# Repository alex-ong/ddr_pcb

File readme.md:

DDR FSR PCB
===

A simple pcb that fits into a smaller footprint than a half-sized breadboard. Measurements are 49mm x 62mm

Uses screw terminals for wires and sip sockets for resistors to make everything tool-less once soldered.

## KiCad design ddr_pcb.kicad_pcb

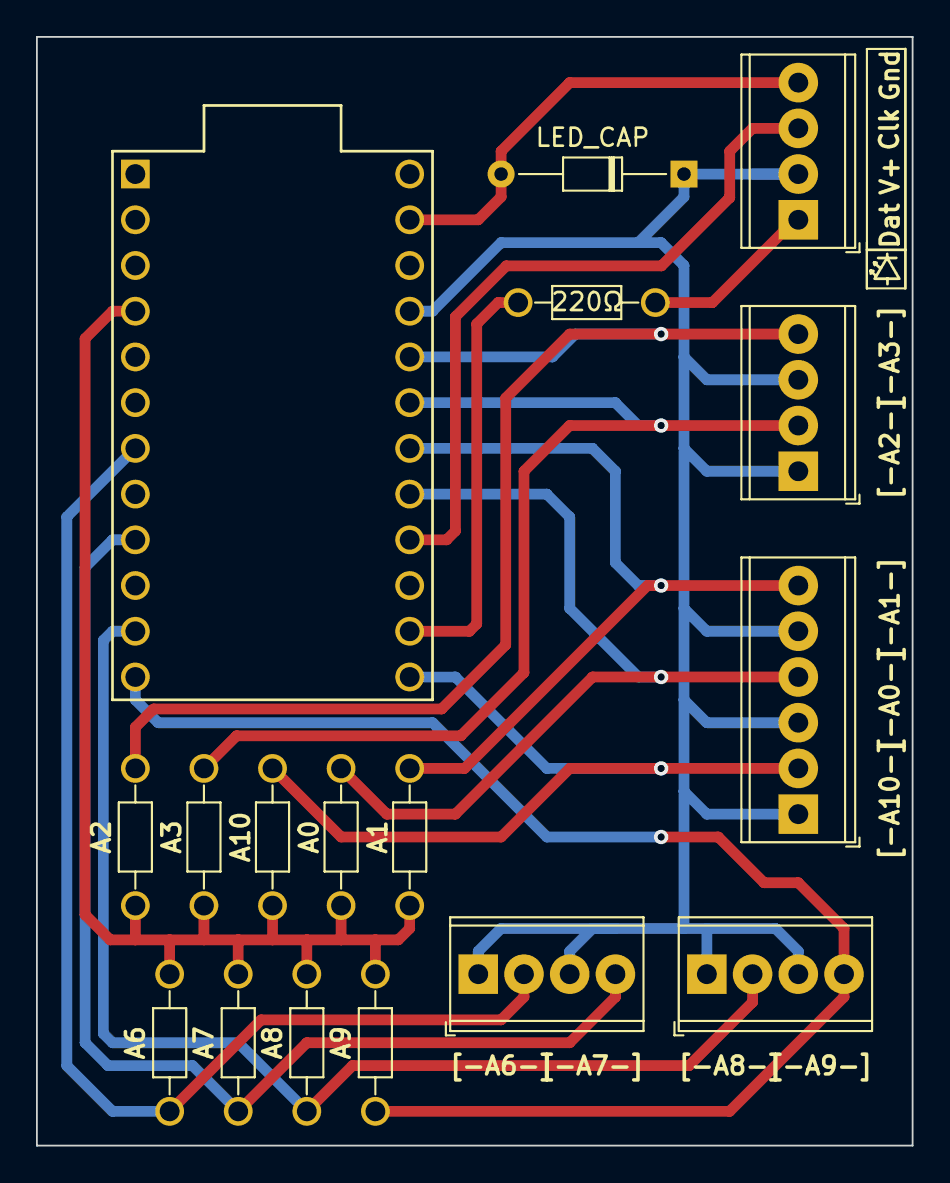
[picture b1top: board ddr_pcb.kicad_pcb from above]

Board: 2 copper layers, 48.7 x 61.6 mm, 17 parts (0 on the bottom side), 15 nets.

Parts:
220Ω: R_Small; R_Axial_DDRPAD_L3.6mm_D1.6mm_P7.62mm_Horizontal
A0, A1, A2, A3, A6, A7, A8, A9, A10: R_Small; R_Axial_DDRPAD_L3.6mm_D1.6mm_P7.62mm_Horizontal
J1, J2, J3, J5: Screw_Terminal_01x04; TerminalBlock_Phoenix_MPT-0,5-4-2.54_1x04_P2.54mm_Horizontal
J4: Screw_Terminal_01x06; TerminalBlock_Phoenix_MPT-0,5-6-2.54_1x06_P2.54mm_Horizontal
LED_CAP: CP; D_DO-34_SOD68_P10.16mm_Horizontal
U1: ProMicro

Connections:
unnamed: 220Ω.1, J5.1
unnamed: 220Ω.2, U1.14
unnamed: A0.1, J4.4, U1.17
unnamed: A0.2, A1.2, A2.2, A3.2, A6.2, A7.2, A8.2, A9.2, A10.2, U1.4
unnamed: A1.1, J4.6, U1.18
unnamed: A2.1, J3.4, U1.20
unnamed: A3.1, J3.2, U1.19
unnamed: A6.1, J2.2, U1.7
unnamed: A7.1, J2.4, U1.9
unnamed: A8.1, J1.2, U1.11
unnamed: A9.1, J1.4, U1.12
unnamed: A10.1, J4.2, U1.13
unnamed: J1.1, J1.3, J2.1, J2.3, J3.1, J3.3, J4.1, J4.3, J4.5, J5.2, LED_CAP.1, U1.21
unnamed: J5.3, U1.16
unnamed: J5.4, LED_CAP.2, U1.23

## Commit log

2021-11-12 new: Finished WIP
2021-11-12 new: Add text to silkscreen
2021-11-12 new: fill in pcb area
2021-11-12 new: add bigger holes for resistors so that we can socket them
2021-11-13 Change resistor to have a bigger hole, fix text size
2021-11-14 new: Ordered through JLCPCB!
2021-11-14 new: Change Capacitor to match real life more
2021-12-15 new: Add extra link for APA102
2021-12-18 new: Leaner and meaner (v2.0)
2021-12-18 new: Updated graphics for the pcb
2022-04-23 new: Update pins to use 15/16 for SPI. Swap Pin1 to dat for non-SPI LEDs
